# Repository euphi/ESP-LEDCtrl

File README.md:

# ESP-LEDCtrl
LED Strip Controller (2x RGB, 1 White) with ESP8266 Homie (MQTT).
Display support (SSD1306 OLED) is work in progress.

## How to Build
  * If not already installed, install Platformio
    * See http://docs.platformio.org/en/latest/installation.html for instructions
    
  * Clone LEDCtrl + necessary libraries into a directory
    * `git clone https://github.com/euphi/ESP-LEDCtrl.git`
    * `git clone https://github.com/marvinroger/homie-esp8266.git`
    * `git clone https://github.com/euphi/HomieNodeCollection.git`
    * `git clone https://github.com/euphi/esp8266-oled-ssd1306.git`
    
  * Link libs into the ESP-LEDCtrl lib directory:
    * `cd ESP-LEDCtrl/lib`
    * `ln -s ../../homie-esp8266 .`
    * `ln -s ../../HomieNodeCollection .`
    * `ln -s ../../esp8266-oled-ssd1306 .`
    * `cd ..`
  
  * Run platformio
    * Ensure working directory is ESP-LEDCtrl and run `pio run` 
    * To upload, use `pio run --target upload`
    
## Outlook
  * Display support
  * touch controller support
  * Support for "set temperature", so it can be used as thermostat.

## Hardware
  * There is a kicad project with a PCB for two RGB outputs and one white channel in the [PCB subdirectory](doc/PCB)
  * 
  * This PCB does not use any SMD parts, so it can easily be built and soldered at home (I created and etched  it with "toner transfer", then soldered the parts).
  * The RGB output uses an ULN2003A as amplifier. This is a Bipolar device with limited power, so don't drive LED strips with it without an RGB signal amplifier.
    * Example signal amplifier on [Amazon](https://www.amazon.de/gp/product/B00E4GVUMS)

  * The white channel uses a FET as driver, so you can drive white LED strips.
  * I2C is available on board. Till now, I used it to connect a HTU21 temperature+humidity sensor to it. I will add a touch controller to control the LEDs locally.
  * Serial Programming Interface available. Auto-Reset into flash mode possible with esptool / platformio using the "ck"-reset method (Connect DTR to GPIO0, RTS to Reset)
  * BOM:
    * ESP-12F (Ai-Thinker) (or ESP-12E)
    * ULN 2003
    * P16NF06L
    * DCDC-Converter (Adjustable, set to 12V -> 3,3V) (DAOKAI® 10PCS Standard Stromversorgungsmodul Adjustable Step down 3A DC DC Converter 1pc New)
    * 3x 1/4 W Resistor (Pull-Up/Down; I used 3,16kΩ)
    * Molex 4 Pin Connectors
    * Molex 3 Pin Connectors
    * 2mm Pin-Header to solder the ESP-12E
    * 2,54mm Pin-Header for Serial/Programming interface (use "ck"-Reset method for esptool).

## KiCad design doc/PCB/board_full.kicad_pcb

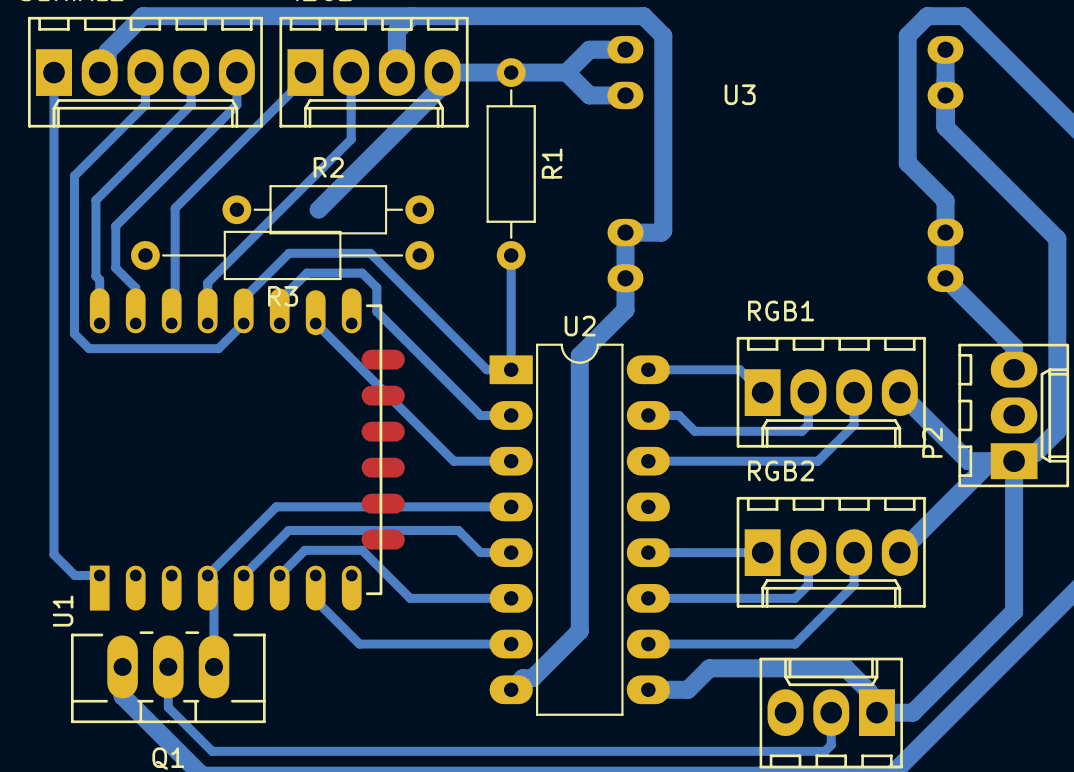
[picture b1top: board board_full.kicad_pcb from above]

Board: 2 copper layers, 13 parts (0 on the bottom side), 22 nets.

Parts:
I2C1: CONN_01X04; Molex_KK-6410-04_04x2.54mm_Straight
P1, P2: CONN_01X03; Molex_KK-6410-03_03x2.54mm_Straight
Q1: Q_NMOS_GDS; TO-220_Neutral123_Vertical_LargePads
R1: 1k8; R_Axial_DIN0207_L6.3mm_D2.5mm_P10.16mm_Horizontal
R2: 1K8; R_Axial_DIN0207_L6.3mm_D2.5mm_P10.16mm_Horizontal
R3: 1K8; R_Axial_DIN0207_L6.3mm_D2.5mm_P15.24mm_Horizontal
RGB1, RGB2: CONN_01X04; Molex_KK-6410-04_04x2.54mm_Straight
SERIAL1: CONN_01X05; Molex_KK-6410-05_05x2.54mm_Straight
U1: ESP-12E
U2: ULN2003A; DIP-16_W7.62mm_LongPads
U3: DCDC

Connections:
+3V3: I2C1.4, R1.1, R2.1, U1.3, U1.8, U3.3
+12V: P1.1, P2.1, RGB1.4, RGB2.4, U2.9, U3.1
/FLASH: R1.2, SERIAL1.3, U1.12, U2.1
/RESET: SERIAL1.1, U1.1
/RX: SERIAL1.5, U1.15
/SCL: I2C1.1, U1.14
/SDA: I2C1.2, U1.13
/TX: SERIAL1.4, U1.16
GND: I2C1.3, P2.3, Q1.3, R3.2, SERIAL1.2, U1.9, U2.8, U3.2, U3.4
unnamed: P1.2, Q1.2
unnamed: Q1.1, U1.4, U2.4
unnamed: R2.2, U1.11, U2.2
unnamed: R3.1, U1.10, U2.3
unnamed: RGB1.1, U2.16
unnamed: RGB1.2, U2.15
unnamed: RGB1.3, U2.14
unnamed: RGB2.1, U2.12
unnamed: RGB2.2, U2.11
unnamed: RGB2.3, U2.10
unnamed: U1.5, U2.5
unnamed: U1.6, U2.6
unnamed: U1.7, U2.7

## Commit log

2016-06-18 Initial (old version for first tests with Homie).
    To be updated to use latest Homie Version and make use of new "virtual"
    features.
2016-08-15 Change to Homie-2.0 git version (no real progress yet)
2016-08-21 Adapted to latest Homie release
2016-11-12 Added second RGB-Node and update to latest platformio
    This version is the first version "in field".
2017-01-09 Added necessary libraries to compile
2017-01-10 Update README.md
    Added intructions how-to build
2017-02-05 Created PCB in Kicad and added to doc directory
    - this includes a change to main.cpp because of change in PIN usage for white LED
2017-02-05 Changed symlinks to real files ... 'doh.
2017-02-05 Added example PNG
2017-02-05 Update readme.md: Add example PCB
2017-02-05 Added resistors to BoM and added info about serial interface
2017-02-05 Added outlook to readme.md
2017-02-05 Added PDF of example schematics
2017-05-07 Updates to hardware (PCB)
2017-05-07 Added Serial debug for OTA
2017-05-07 OTA Support + architecture improvements for OLED Display
2017-05-12 Version bump (due to updated libs) + change of init order for Serial.
2017-05-16 Enable travis CI + change to example PCB
2017-05-16 No need anymore for Automaton
2017-05-16 No more automatic upload. Use --target=upload instead.
2017-08-05 Improved build scripts
2017-08-05 Fix Eclipse C++ indexer
2017-08-06 Build improvements
2017-12-08 Improvments for travis-ci
2017-12-08 Removed unneeded "InputController.h"
2017-12-17 platformio: Added dependency to my HomieLoggerNode
    Thanks to travis-ci for noting this :-)
    Furthemore, dependency to HomieNodeCollection was set to latest release in platformio repository (instead of latest github sources)
2019-01-11 commented out UI code. Adapted to one RGB-Channel-version
